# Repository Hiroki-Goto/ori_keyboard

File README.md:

# My best original keyboard
This repository is development one of original keyboard
for me (The name is undecided yet).

Software is developed by [qmk firmware](https://github.com/qmk/qmk_firmware).

## We can't find avr-gcc command
After qmk setupping, if you use mac OS, avr-gcc may be not found.
Please refer [this WEB site](https://bytes.usc.edu/ee109/macos-64-bit-toolchain/).

## Constitution keyboard
These module are connected with Pro micro as figure.
- 2 I/O expanders (scanning key matrix each other)
- Displaying current layer on OLED module
- Pointing device (uncertain)
    - Track ball module 
    - joystick 

There may be others.....

## Development record
- [software](https://github.com/Hiroki-Goto/qmk_firmware/tree/hiro_test)  

- [Development record](https://github.com/Hiroki-Goto/ori_keyboard/issues)

# Licence

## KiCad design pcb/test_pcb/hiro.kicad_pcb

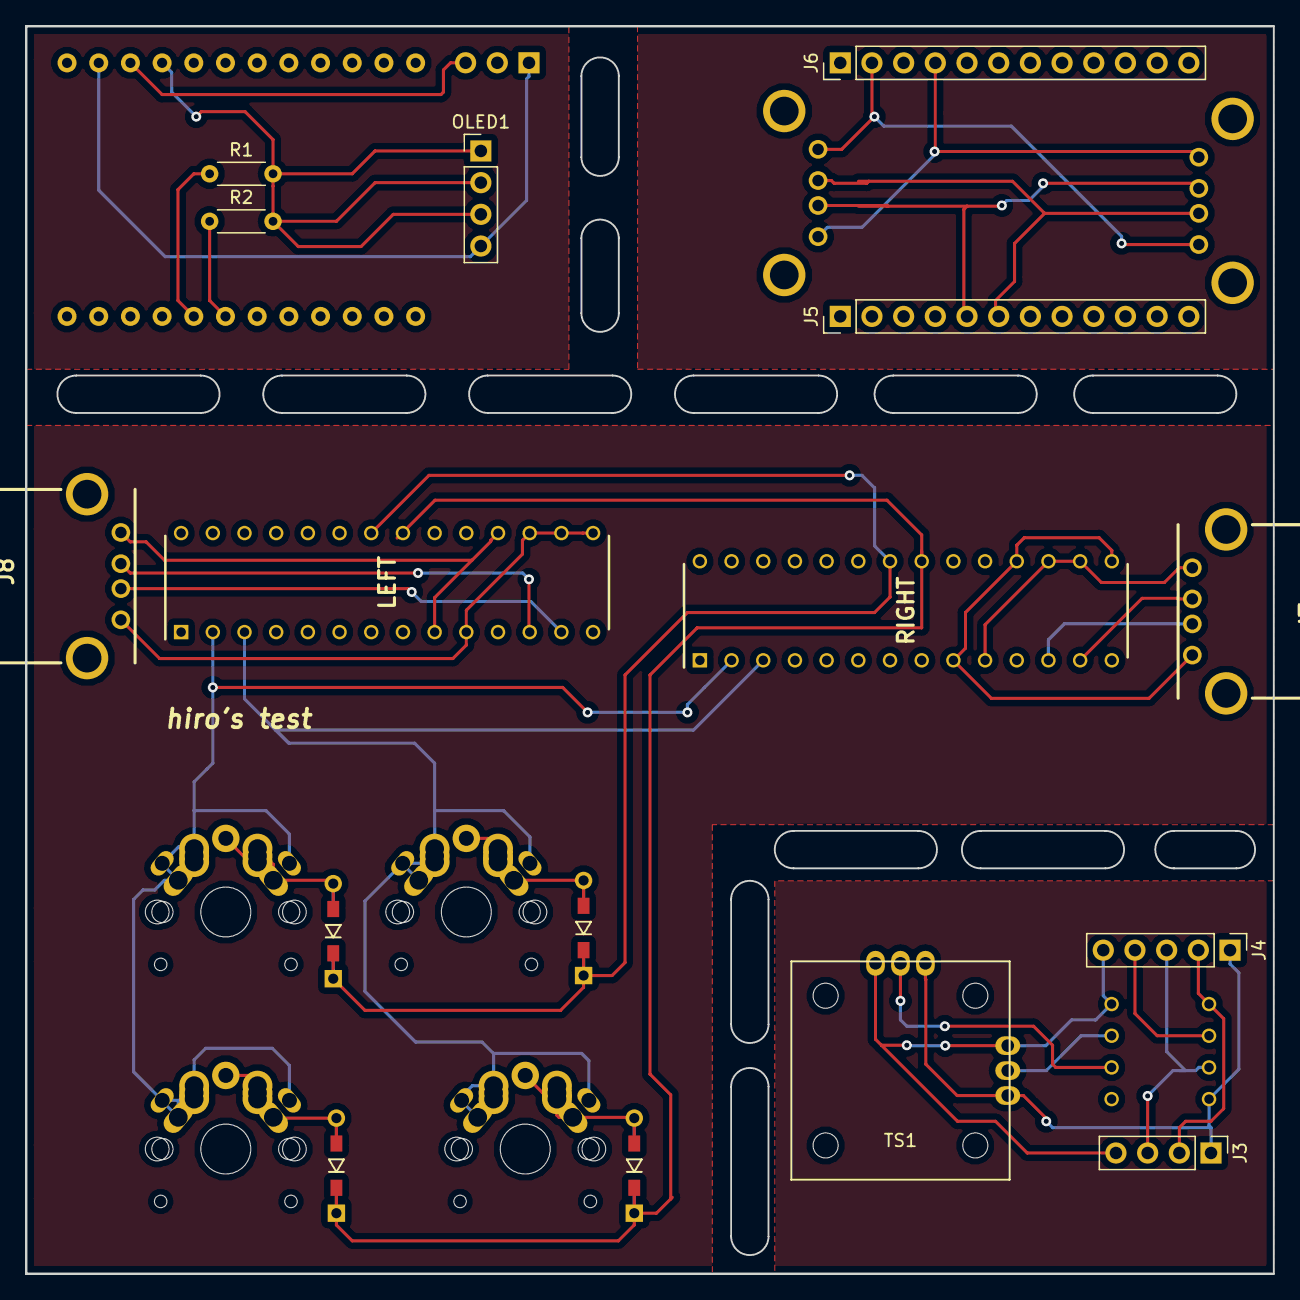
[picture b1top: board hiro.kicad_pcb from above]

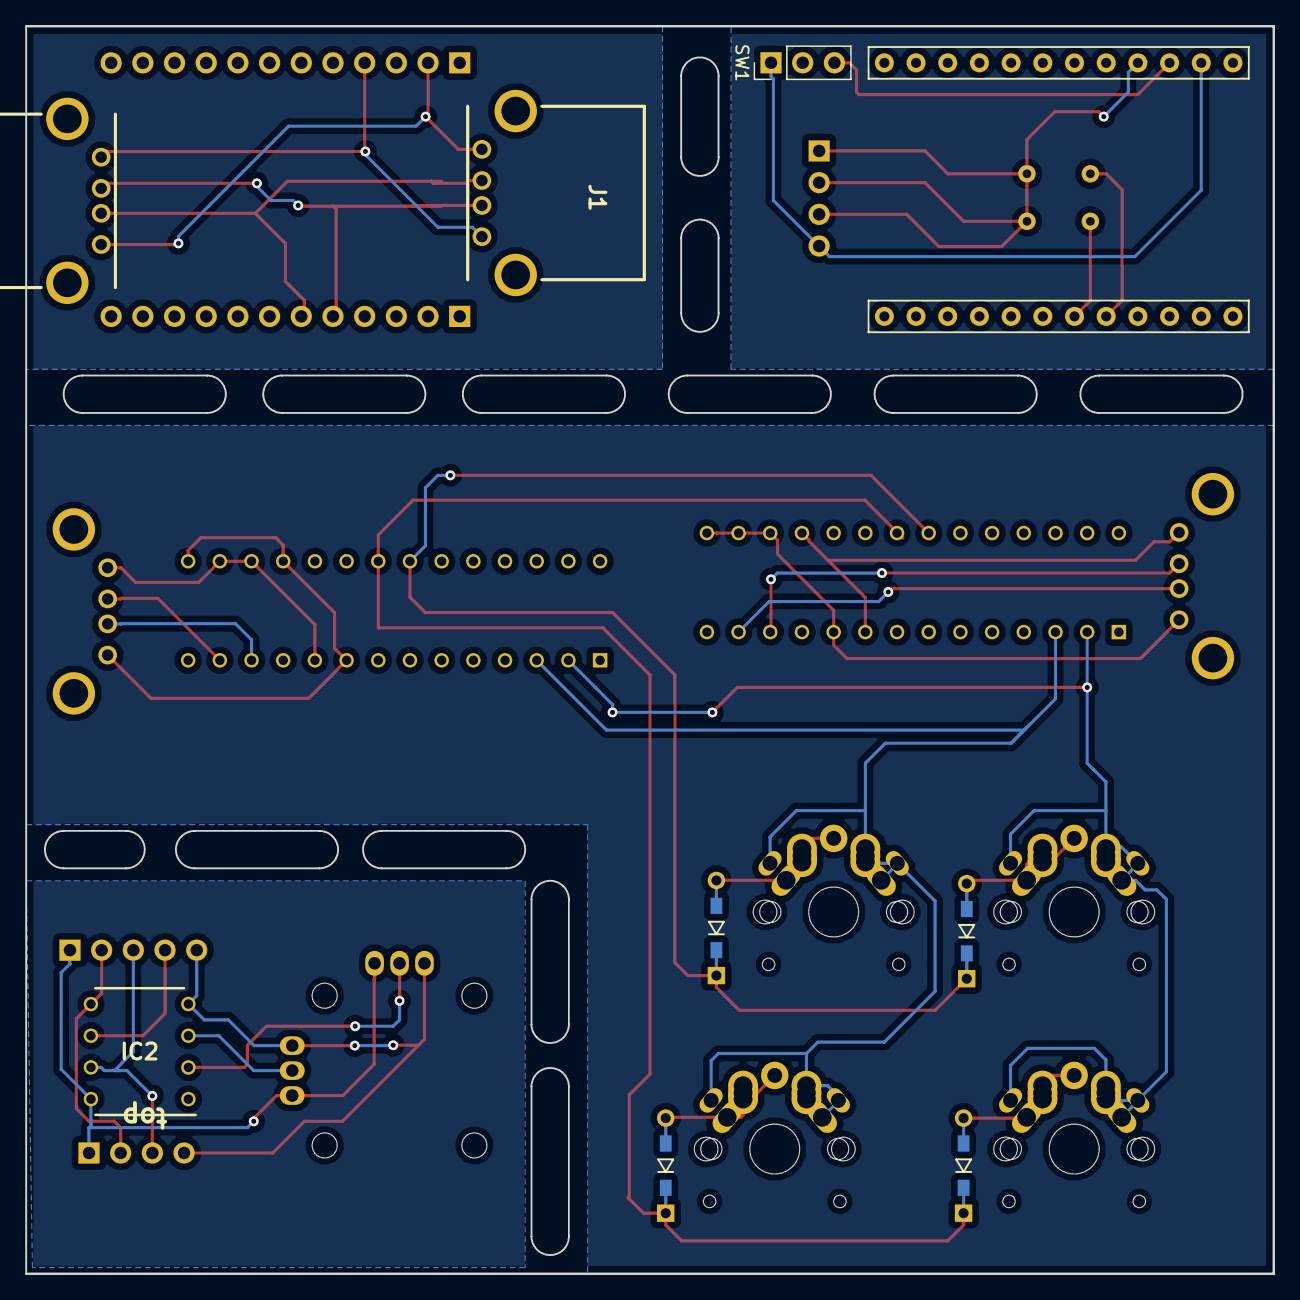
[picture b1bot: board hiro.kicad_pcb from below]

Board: 2 copper layers, 100.0 x 100.0 mm, 25 parts (4 on the bottom side), 30 nets.

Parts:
D1, D2, D3, D4: 1N4148; diode
IC1: DEV-12587; no_moge_micle
IC2: ATTINY85-20PU; DIP781W56P254L950H533Q8N
J1, J2, J7, J8: 614004190021; USB-2.0-TYPE-A
J3: Conn_01x04; PinHeader_1x04_P2.54mm_Vertical
J4: Conn_01x05; PinHeader_1x05_P2.54mm_Vertical
J5, J6: Conn_01x12; PinHeader_1x12_P2.54mm_Vertical
LEFT: MCP23017-E_SP; DIP794W56P254L3486H508Q28N
OLED1: Conn_01x04; PinHeader_1x04_P2.54mm_Vertical
R1, R2: R; R_Axial_DIN0204_L3.6mm_D1.6mm_P5.08mm_Horizontal
RIGHT: MCP23017-E_SP; DIP794W56P254L3486H508Q28N
SW1: SW_DIP_x02; PinHeader_1x03_P2.54mm_Vertical
SW2, SW3, SW4: SW_PUSH; key_switch_1u
SW5: SW_PUSH; key_switch_15u
TS1: JT8P-3.2T-B10K-1-16Y

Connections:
0: J7.4, J8.4, LEFT.10, LEFT.15, LEFT.16, LEFT.17, RIGHT.10, RIGHT.16, RIGHT.17
5V: IC1.21, OLED1.1, OLED1.2, OLED1.3, R1.2, R2.2
+5V: J7.1, J8.1, LEFT.9, LEFT.18, RIGHT.9, RIGHT.15, RIGHT.18
/tiny/GND: IC2.4, J3.4, J4.5, TS1.3
/tiny/MISO: IC2.6, J4.4
/tiny/TINY_5: IC2.5, J3.2, J4.2
/tiny/TINY_7: IC2.7, J3.3, J4.3
/tiny/VCC: IC2.8, J3.1, J4.1, TS1.1
/tiny/x: IC2.2, TS1.2
/tiny/y: IC2.3, TS1.4
B_5V: J1.1, J2.1, J6.4
B_GND: J1.4, J2.4, J6.2
B_SCL: J1.3, J2.3, J5.6
B_SDA: J1.2, J2.2, J5.5
GND: IC1.23, OLED1.4, SW1.1, SW1.2
unnamed: D1.2, SW2.2
unnamed: D2.2, SW3.2
unnamed: D3.2, SW4.2
unnamed: D4.2, SW5.2
unnamed: IC1.5, R1.1
unnamed: IC1.6, R2.1
unnamed: J7.2, RIGHT.12
unnamed: J7.3, RIGHT.13
unnamed: J8.2, LEFT.12
unnamed: J8.3, LEFT.13
RST: IC1.22, SW1.3
col0: D1.1, D3.1, LEFT.22, RIGHT.22
col1: D2.1, D4.1, LEFT.21, RIGHT.21
row0: LEFT.2, RIGHT.2, SW2.1, SW3.1
row1: LEFT.3, RIGHT.3, SW4.1, SW5.1

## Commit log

2018-05-21 push key
2018-05-22 add leyer
2018-05-23 OLEDに表示する機能の追加
2018-05-26 シリアル通信の実装
2018-06-09 i2cでも通信ができた
2018-06-09 レイヤー機能のバグ修正
2018-06-09 初期化のバグ修正
2019-05-18 qmkに対応中
2019-05-18 scan matrix using only mcp23017
2019-05-19 rewrite readme
2019-05-19 add licence
2019-05-19 add LICENSE
2019-05-19 can scan matrix as 1x2
2019-05-26 複数に対応
2019-07-14 change readme figure
2019-07-14 Create LICENSE
2019-07-14 add licence at readme
2020-03-15 ソース上げ
2020-04-05 行の開始位置などがおかしい問題の修正
2021-01-12 qmkのビルドできない問題を記載
